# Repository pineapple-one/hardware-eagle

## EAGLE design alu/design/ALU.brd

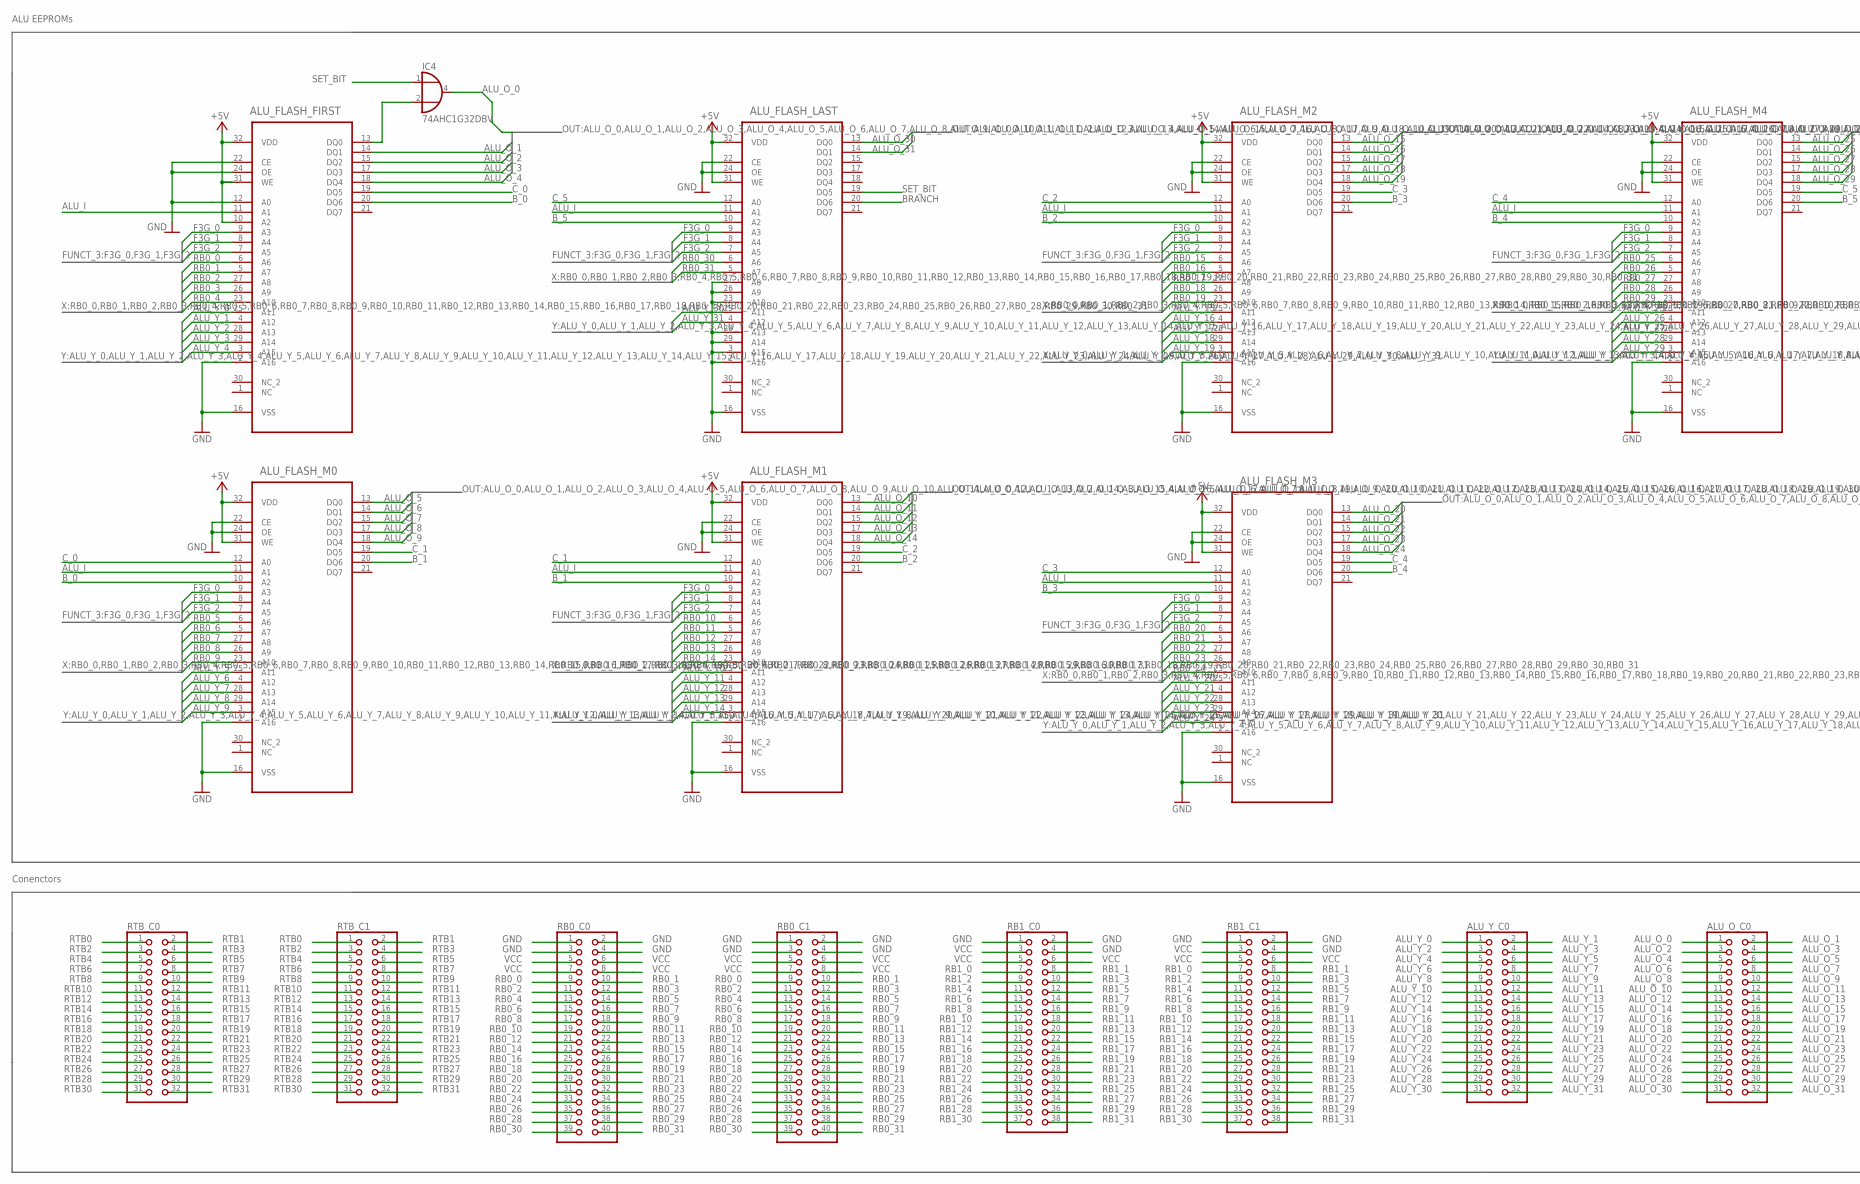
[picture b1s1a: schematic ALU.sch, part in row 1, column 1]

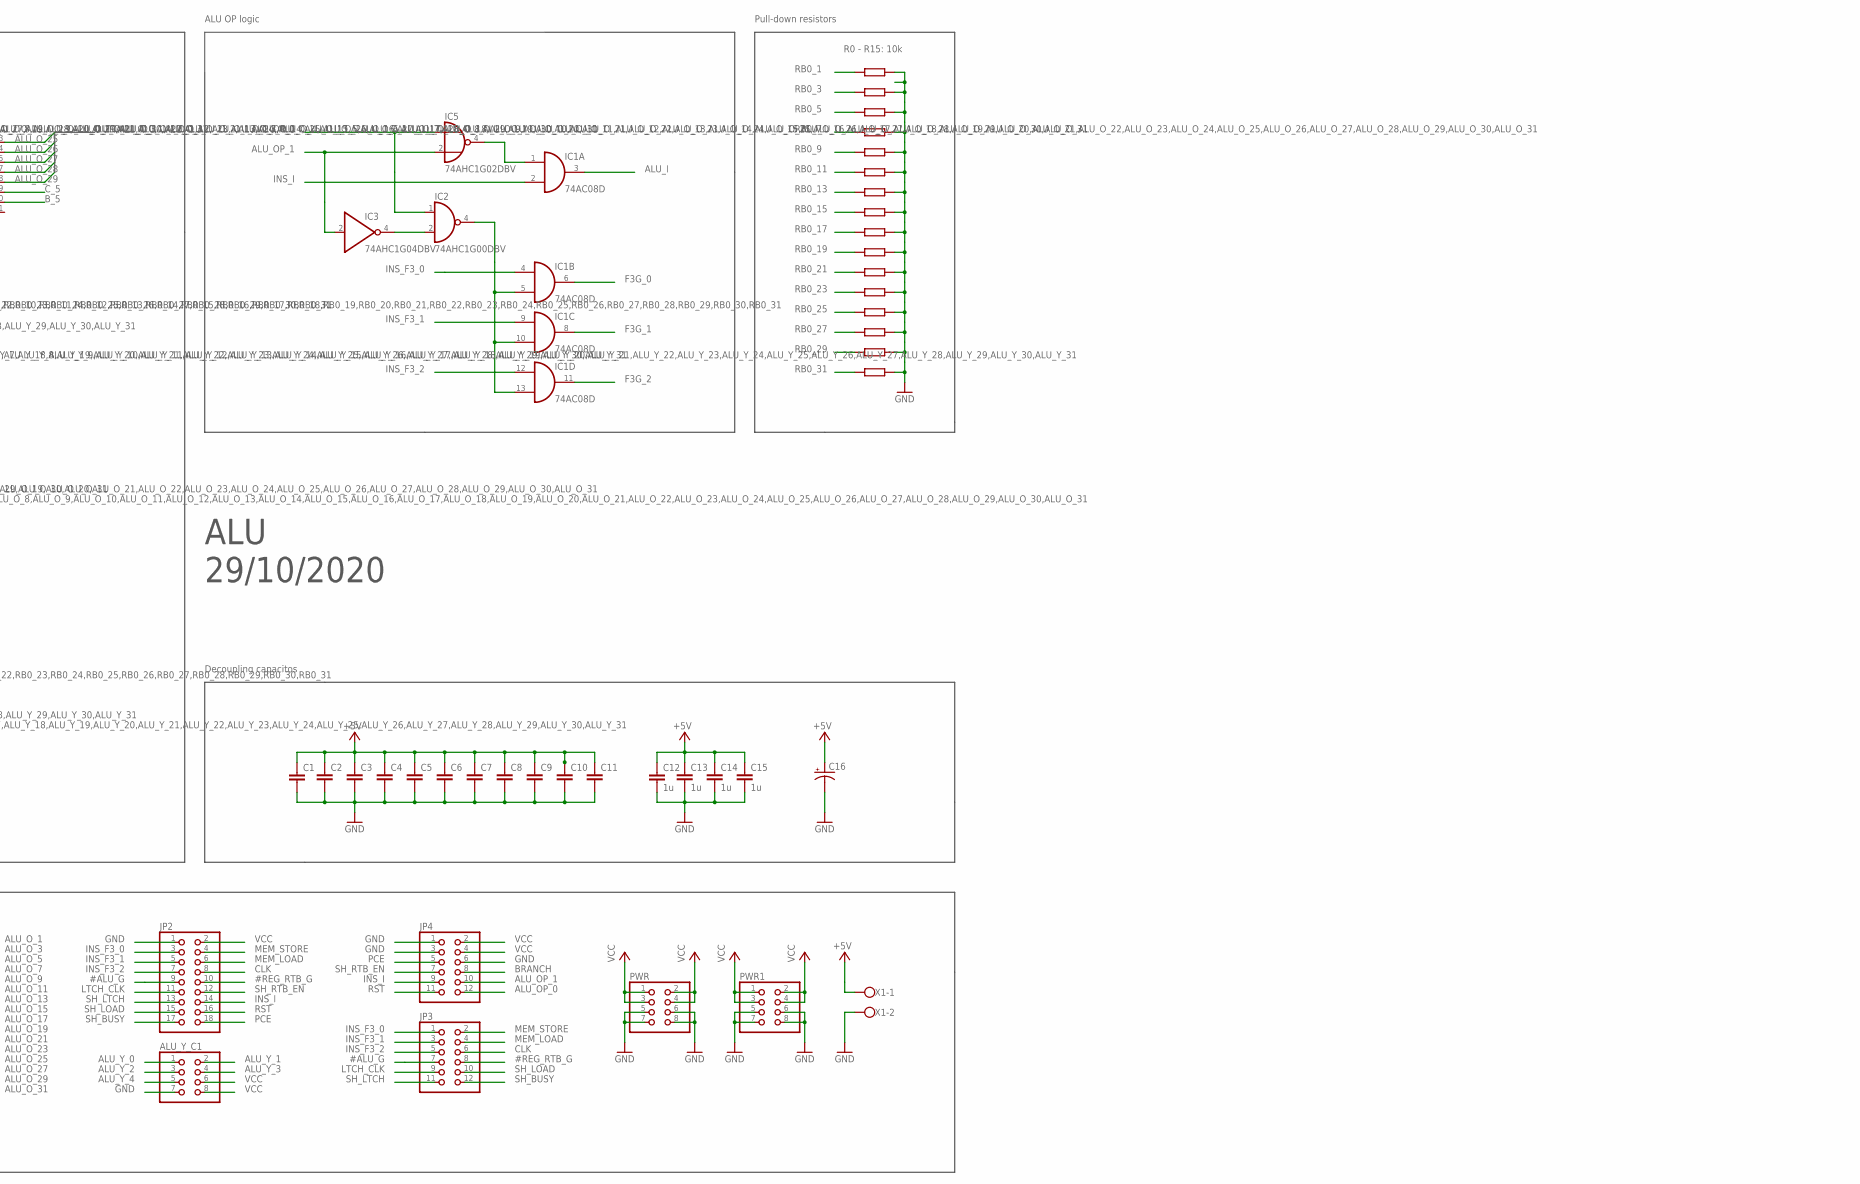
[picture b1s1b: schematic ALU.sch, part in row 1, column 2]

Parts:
ALU_FLASH_FIRST: SST39SF010A-70-4I-NHEPLCC32; S32
ALU_FLASH_LAST: SST39SF010A-70-4I-NHEPLCC32; S32
ALU_FLASH_M0, ALU_FLASH_M1, ALU_FLASH_M2, ALU_FLASH_M3, ALU_FLASH_M4: SST39SF010A-70-4I-NHEPLCC32; S32
ALU_O_C0: PINHD-2X16; 2X16
ALU_Y_C0: PINHD-2X16; 2X16
ALU_Y_C1: PINHD-2X4; 2X04
C1, C2, C3, C4, C5, C6, C7, C8, C9, C10, C11: C-EUC0805; C0805
C12, C13, C14, C15: 1u; C0805
C16: CAPACITOR-P153CLV-1010; 153CLV-1010
IC1: 74AC08D; SO14
IC2: 74AHC1G00DBV; SOT23-5
IC3: 74AHC1G04DBV; SOT23-5
IC4: 74AHC1G32DBV; SOT23-5
IC5: 74AHC1G02DBV; SOT23-5
JP2: PINHD-2X9; 2X09
JP3, JP4: PINHD-2X6; 2X06
PWR, PWR1: PINHD-2X4; 2X04
R0, R1, R2, R3, R4, R5, R6, R7, R8, R9, R10, R11, R12, R13, R14, R15: R-EU_R0805; R0805
RB0_C0, RB0_C1: PINHD-2X20; 2X20
RB1_C0, RB1_C1: PINHD-2X19; 2X19
RTB_C0, RTB_C1: PINHD-2X16; 2X16
X1: W237-102

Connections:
#ALU_G: JP2.9, JP3.7
#REG_RTB_G: JP2.10, JP3.8
ALU_I: ALU_FLASH_FIRST.11 (A1), ALU_FLASH_LAST.11 (A1), ALU_FLASH_M0.11 (A1), ALU_FLASH_M1.11 (A1), ALU_FLASH_M2.11 (A1), ALU_FLASH_M3.11 (A1), ALU_FLASH_M4.11 (A1), IC1.3 (O)
ALU_OP_0: IC2.1 (I0), IC5.1 (I0), JP4.12
ALU_OP_1: IC3.2 (I), IC5.2 (I1), JP4.10
ALU_O_0: ALU_O_C0.1, IC4.4 (O)
ALU_O_1: ALU_FLASH_FIRST.14 (DQ1), ALU_O_C0.2
ALU_O_2: ALU_FLASH_FIRST.15 (DQ2), ALU_O_C0.3
ALU_O_3: ALU_FLASH_FIRST.17 (DQ3), ALU_O_C0.4
ALU_O_4: ALU_FLASH_FIRST.18 (DQ4), ALU_O_C0.5
ALU_O_5: ALU_FLASH_M0.13 (DQ0), ALU_O_C0.6
ALU_O_6: ALU_FLASH_M0.14 (DQ1), ALU_O_C0.7
ALU_O_7: ALU_FLASH_M0.15 (DQ2), ALU_O_C0.8
ALU_O_8: ALU_FLASH_M0.17 (DQ3), ALU_O_C0.9
ALU_O_9: ALU_FLASH_M0.18 (DQ4), ALU_O_C0.10
ALU_O_10: ALU_FLASH_M1.13 (DQ0), ALU_O_C0.11
ALU_O_11: ALU_FLASH_M1.14 (DQ1), ALU_O_C0.12
ALU_O_12: ALU_FLASH_M1.15 (DQ2), ALU_O_C0.13
ALU_O_13: ALU_FLASH_M1.17 (DQ3), ALU_O_C0.14
ALU_O_14: ALU_FLASH_M1.18 (DQ4), ALU_O_C0.15
ALU_O_15: ALU_FLASH_M2.13 (DQ0), ALU_O_C0.16
ALU_O_16: ALU_FLASH_M2.14 (DQ1), ALU_O_C0.17
ALU_O_17: ALU_FLASH_M2.15 (DQ2), ALU_O_C0.18
ALU_O_18: ALU_FLASH_M2.17 (DQ3), ALU_O_C0.19
ALU_O_19: ALU_FLASH_M2.18 (DQ4), ALU_O_C0.20
ALU_O_20: ALU_FLASH_M3.13 (DQ0), ALU_O_C0.21
ALU_O_21: ALU_FLASH_M3.14 (DQ1), ALU_O_C0.22
ALU_O_22: ALU_FLASH_M3.15 (DQ2), ALU_O_C0.23
ALU_O_23: ALU_FLASH_M3.17 (DQ3), ALU_O_C0.24
ALU_O_24: ALU_FLASH_M3.18 (DQ4), ALU_O_C0.25
ALU_O_25: ALU_FLASH_M4.13 (DQ0), ALU_O_C0.26
ALU_O_26: ALU_FLASH_M4.14 (DQ1), ALU_O_C0.27
ALU_O_27: ALU_FLASH_M4.15 (DQ2), ALU_O_C0.28
ALU_O_28: ALU_FLASH_M4.17 (DQ3), ALU_O_C0.29
ALU_O_29: ALU_FLASH_M4.18 (DQ4), ALU_O_C0.30
ALU_O_30: ALU_FLASH_LAST.13 (DQ0), ALU_O_C0.31
ALU_O_31: ALU_FLASH_LAST.14 (DQ1), ALU_O_C0.32
ALU_Y_0: ALU_FLASH_FIRST.25 (A11), ALU_Y_C0.1, ALU_Y_C1.1
ALU_Y_1: ALU_FLASH_FIRST.4 (A12), ALU_Y_C0.2, ALU_Y_C1.2
ALU_Y_2: ALU_FLASH_FIRST.28 (A13), ALU_Y_C0.3, ALU_Y_C1.3
ALU_Y_3: ALU_FLASH_FIRST.29 (A14), ALU_Y_C0.4, ALU_Y_C1.4
ALU_Y_4: ALU_FLASH_FIRST.3 (A15), ALU_Y_C0.5, ALU_Y_C1.5
ALU_Y_5: ALU_FLASH_M0.25 (A11), ALU_Y_C0.6
ALU_Y_6: ALU_FLASH_M0.4 (A12), ALU_Y_C0.7
ALU_Y_7: ALU_FLASH_M0.28 (A13), ALU_Y_C0.8
ALU_Y_8: ALU_FLASH_M0.29 (A14), ALU_Y_C0.9
ALU_Y_9: ALU_FLASH_M0.3 (A15), ALU_Y_C0.10
ALU_Y_10: ALU_FLASH_M1.25 (A11), ALU_Y_C0.11
ALU_Y_11: ALU_FLASH_M1.4 (A12), ALU_Y_C0.12
ALU_Y_12: ALU_FLASH_M1.28 (A13), ALU_Y_C0.13
ALU_Y_13: ALU_FLASH_M1.29 (A14), ALU_Y_C0.14
ALU_Y_14: ALU_FLASH_M1.3 (A15), ALU_Y_C0.15
ALU_Y_15: ALU_FLASH_M2.25 (A11), ALU_Y_C0.16
ALU_Y_16: ALU_FLASH_M2.4 (A12), ALU_Y_C0.17
ALU_Y_17: ALU_FLASH_M2.28 (A13), ALU_Y_C0.18
ALU_Y_18: ALU_FLASH_M2.29 (A14), ALU_Y_C0.19
ALU_Y_19: ALU_FLASH_M2.3 (A15), ALU_Y_C0.20
ALU_Y_20: ALU_FLASH_M3.25 (A11), ALU_Y_C0.21
ALU_Y_21: ALU_FLASH_M3.4 (A12), ALU_Y_C0.22
ALU_Y_22: ALU_FLASH_M3.28 (A13), ALU_Y_C0.23
ALU_Y_23: ALU_FLASH_M3.29 (A14), ALU_Y_C0.24
ALU_Y_24: ALU_FLASH_M3.3 (A15), ALU_Y_C0.25
ALU_Y_25: ALU_FLASH_M4.25 (A11), ALU_Y_C0.26
ALU_Y_26: ALU_FLASH_M4.4 (A12), ALU_Y_C0.27
ALU_Y_27: ALU_FLASH_M4.28 (A13), ALU_Y_C0.28
ALU_Y_28: ALU_FLASH_M4.29 (A14), ALU_Y_C0.29
ALU_Y_29: ALU_FLASH_M4.3 (A15), ALU_Y_C0.30
ALU_Y_30: ALU_FLASH_LAST.25 (A11), ALU_Y_C0.31
ALU_Y_31: ALU_FLASH_LAST.4 (A12), ALU_Y_C0.32
BRANCH: ALU_FLASH_LAST.20 (DQ6), JP4.8
B_0: ALU_FLASH_FIRST.20 (DQ6), ALU_FLASH_M0.10 (A2)
B_1: ALU_FLASH_M0.20 (DQ6), ALU_FLASH_M1.10 (A2)
B_2: ALU_FLASH_M1.20 (DQ6), ALU_FLASH_M2.10 (A2)
B_3: ALU_FLASH_M2.20 (DQ6), ALU_FLASH_M3.10 (A2)
B_4: ALU_FLASH_M3.20 (DQ6), ALU_FLASH_M4.10 (A2)
B_5: ALU_FLASH_LAST.10 (A2), ALU_FLASH_M4.20 (DQ6)
CLK: JP2.8, JP3.6
C_0: ALU_FLASH_FIRST.19 (DQ5), ALU_FLASH_M0.12 (A0)
C_1: ALU_FLASH_M0.19 (DQ5), ALU_FLASH_M1.12 (A0)
C_2: ALU_FLASH_M1.19 (DQ5), ALU_FLASH_M2.12 (A0)
C_3: ALU_FLASH_M2.19 (DQ5), ALU_FLASH_M3.12 (A0)
C_4: ALU_FLASH_M3.19 (DQ5), ALU_FLASH_M4.12 (A0)
C_5: ALU_FLASH_LAST.12 (A0), ALU_FLASH_M4.19 (DQ5)
F3G_0: ALU_FLASH_FIRST.9 (A3), ALU_FLASH_LAST.9 (A3), ALU_FLASH_M0.9 (A3), ALU_FLASH_M1.9 (A3), ALU_FLASH_M2.9 (A3), ALU_FLASH_M3.9 (A3), ALU_FLASH_M4.9 (A3), IC1.6 (O)
F3G_1: ALU_FLASH_FIRST.8 (A4), ALU_FLASH_LAST.8 (A4), ALU_FLASH_M0.8 (A4), ALU_FLASH_M1.8 (A4), ALU_FLASH_M2.8 (A4), ALU_FLASH_M3.8 (A4), ALU_FLASH_M4.8 (A4), IC1.8 (O)
F3G_2: ALU_FLASH_FIRST.7 (A5), ALU_FLASH_LAST.7 (A5), ALU_FLASH_M0.7 (A5), ALU_FLASH_M1.7 (A5), ALU_FLASH_M2.7 (A5), ALU_FLASH_M3.7 (A5), ALU_FLASH_M4.7 (A5), IC1.11 (O)
GND: ALU_FLASH_FIRST.2 (A16), ALU_FLASH_FIRST.12 (A0), ALU_FLASH_FIRST.16 (VSS), ALU_FLASH_FIRST.22 (CE), ALU_FLASH_FIRST.24 (OE), ALU_FLASH_LAST.2 (A16), ALU_FLASH_LAST.3 (A15), ALU_FLASH_LAST.16 (VSS), ALU_FLASH_LAST.22 (CE), ALU_FLASH_LAST.23 (A10), ALU_FLASH_LAST.24 (OE), ALU_FLASH_LAST.26 (A9), ALU_FLASH_LAST.27 (A8), ALU_FLASH_LAST.28 (A13), ALU_FLASH_LAST.29 (A14), ALU_FLASH_M0.2 (A16), ALU_FLASH_M0.16 (VSS), ALU_FLASH_M0.22 (CE), ALU_FLASH_M0.24 (OE), ALU_FLASH_M1.2 (A16), ALU_FLASH_M1.16 (VSS), ALU_FLASH_M1.22 (CE), ALU_FLASH_M1.24 (OE), ALU_FLASH_M2.2 (A16), ALU_FLASH_M2.16 (VSS), ALU_FLASH_M2.22 (CE), ALU_FLASH_M2.24 (OE), ALU_FLASH_M3.2 (A16), ALU_FLASH_M3.16 (VSS), ALU_FLASH_M3.22 (CE), ALU_FLASH_M3.24 (OE), ALU_FLASH_M4.2 (A16), ALU_FLASH_M4.16 (VSS), ALU_FLASH_M4.22 (CE), ALU_FLASH_M4.24 (OE), ALU_Y_C1.7, C1.2, C2.2, C3.2, C4.2, C5.2, C6.2, C7.2, C8.2, C9.2, C10.2, C11.2, C12.2, C13.2, C14.2, C15.2, C16.-, IC1.7 (GND), IC2.3 (GND), IC3.3 (GND), IC4.3 (GND), IC5.3 (GND), JP2.1, JP4.1, JP4.3, JP4.6, PWR.5, PWR.6, PWR.7, PWR.8, PWR1.5, PWR1.6, PWR1.7, PWR1.8, R0.2, R1.2, R2.2, R3.2, R4.2, R5.2, R6.2, R7.2, R8.2, R9.2, R10.2, R11.2, R12.2, R13.2, R14.2, R15.2, RB0_C0.1, RB0_C0.2, RB0_C0.3, RB0_C0.4, RB0_C1.1, RB0_C1.2, RB0_C1.3, RB0_C1.4, RB1_C0.1, RB1_C0.2, RB1_C0.4, RB1_C1.1, RB1_C1.2, RB1_C1.4, X1.2
INS_F3_0: IC1.4 (I0), JP2.3, JP3.1
INS_F3_1: IC1.9 (I0), JP2.5, JP3.3
INS_F3_2: IC1.12 (I0), JP2.7, JP3.5
INS_I: IC1.2 (I1), JP2.14, JP4.9
LTCH_CLK: JP2.11, JP3.9
MEM_LOAD: JP2.6, JP3.4
MEM_STORE: JP2.4, JP3.2
unnamed: ALU_FLASH_FIRST.13 (DQ0), IC4.2 (I1)
unnamed: IC1.5 (I1), IC1.10 (I1), IC1.13 (I1), IC2.4 (O)
unnamed: IC2.2 (I1), IC3.4 (O)
unnamed: IC1.1 (I0), IC5.4 (O)
PCE: JP2.18, JP4.5
RB0_0: ALU_FLASH_FIRST.6 (A6), RB0_C0.9, RB0_C1.9
RB0_1: ALU_FLASH_FIRST.5 (A7), R0.1, RB0_C0.10, RB0_C1.10
RB0_2: ALU_FLASH_FIRST.27 (A8), RB0_C0.11, RB0_C1.11
RB0_3: ALU_FLASH_FIRST.26 (A9), R1.1, RB0_C0.12, RB0_C1.12
RB0_4: ALU_FLASH_FIRST.23 (A10), RB0_C0.13, RB0_C1.13
RB0_5: ALU_FLASH_M0.6 (A6), R2.1, RB0_C0.14, RB0_C1.14
RB0_6: ALU_FLASH_M0.5 (A7), RB0_C0.15, RB0_C1.15
RB0_7: ALU_FLASH_M0.27 (A8), R3.1, RB0_C0.16, RB0_C1.16
RB0_8: ALU_FLASH_M0.26 (A9), RB0_C0.17, RB0_C1.17
RB0_9: ALU_FLASH_M0.23 (A10), R4.1, RB0_C0.18, RB0_C1.18
RB0_10: ALU_FLASH_M1.6 (A6), RB0_C0.19, RB0_C1.19
RB0_11: ALU_FLASH_M1.5 (A7), R5.1, RB0_C0.20, RB0_C1.20
RB0_12: ALU_FLASH_M1.27 (A8), RB0_C0.21, RB0_C1.21
RB0_13: ALU_FLASH_M1.26 (A9), R6.1, RB0_C0.22, RB0_C1.22
RB0_14: ALU_FLASH_M1.23 (A10), RB0_C0.23, RB0_C1.23
RB0_15: ALU_FLASH_M2.6 (A6), R7.1, RB0_C0.24, RB0_C1.24
RB0_16: ALU_FLASH_M2.5 (A7), RB0_C0.25, RB0_C1.25
RB0_17: ALU_FLASH_M2.27 (A8), R8.1, RB0_C0.26, RB0_C1.26
RB0_18: ALU_FLASH_M2.26 (A9), RB0_C0.27, RB0_C1.27
RB0_19: ALU_FLASH_M2.23 (A10), R9.1, RB0_C0.28, RB0_C1.28
RB0_20: ALU_FLASH_M3.6 (A6), RB0_C0.29, RB0_C1.29
RB0_21: ALU_FLASH_M3.5 (A7), R10.1, RB0_C0.30, RB0_C1.30
RB0_22: ALU_FLASH_M3.27 (A8), RB0_C0.31, RB0_C1.31
RB0_23: ALU_FLASH_M3.26 (A9), R11.1, RB0_C0.32, RB0_C1.32
RB0_24: ALU_FLASH_M3.23 (A10), RB0_C0.33, RB0_C1.33
RB0_25: ALU_FLASH_M4.6 (A6), R12.1, RB0_C0.34, RB0_C1.34
RB0_26: ALU_FLASH_M4.5 (A7), RB0_C0.35, RB0_C1.35
RB0_27: ALU_FLASH_M4.27 (A8), R13.1, RB0_C0.36, RB0_C1.36
RB0_28: ALU_FLASH_M4.26 (A9), RB0_C0.37, RB0_C1.37
RB0_29: ALU_FLASH_M4.23 (A10), R14.1, RB0_C0.38, RB0_C1.38
RB0_30: ALU_FLASH_LAST.6 (A6), RB0_C0.39, RB0_C1.39
RB0_31: ALU_FLASH_LAST.5 (A7), R15.1, RB0_C0.40, RB0_C1.40
RB1_0: RB1_C0.7, RB1_C1.7
RB1_1: RB1_C0.8, RB1_C1.8
RB1_2: RB1_C0.9, RB1_C1.9
RB1_3: RB1_C0.10, RB1_C1.10
RB1_4: RB1_C0.11, RB1_C1.11
RB1_5: RB1_C0.12, RB1_C1.12
RB1_6: RB1_C0.13, RB1_C1.13
RB1_7: RB1_C0.14, RB1_C1.14
RB1_8: RB1_C0.15, RB1_C1.15
RB1_9: RB1_C0.16, RB1_C1.16
RB1_10: RB1_C0.17, RB1_C1.17
RB1_11: RB1_C0.18, RB1_C1.18
RB1_12: RB1_C0.19, RB1_C1.19
RB1_13: RB1_C0.20, RB1_C1.20
RB1_14: RB1_C0.21, RB1_C1.21
RB1_15: RB1_C0.22, RB1_C1.22
RB1_16: RB1_C0.23, RB1_C1.23
RB1_17: RB1_C0.24, RB1_C1.24
RB1_18: RB1_C0.25, RB1_C1.25
RB1_19: RB1_C0.26, RB1_C1.26
RB1_20: RB1_C0.27, RB1_C1.27
RB1_21: RB1_C0.28, RB1_C1.28
RB1_22: RB1_C0.29, RB1_C1.29
RB1_23: RB1_C0.30, RB1_C1.30
RB1_24: RB1_C0.31, RB1_C1.31
RB1_25: RB1_C0.32, RB1_C1.32
RB1_26: RB1_C0.33, RB1_C1.33
RB1_27: RB1_C0.34, RB1_C1.34
RB1_28: RB1_C0.35, RB1_C1.35
RB1_29: RB1_C0.36, RB1_C1.36
RB1_30: RB1_C0.37, RB1_C1.37
RB1_31: RB1_C0.38, RB1_C1.38
RST: JP2.16, JP4.11
RTB0: RTB_C0.1, RTB_C1.1
RTB1: RTB_C0.2, RTB_C1.2
RTB2: RTB_C0.3, RTB_C1.3
RTB3: RTB_C0.4, RTB_C1.4
RTB4: RTB_C0.5, RTB_C1.5
RTB5: RTB_C0.6, RTB_C1.6
RTB6: RTB_C0.7, RTB_C1.7
RTB7: RTB_C0.8, RTB_C1.8
RTB8: RTB_C0.9, RTB_C1.9
RTB9: RTB_C0.10, RTB_C1.10
RTB10: RTB_C0.11, RTB_C1.11
RTB11: RTB_C0.12, RTB_C1.12
RTB12: RTB_C0.13, RTB_C1.13
RTB13: RTB_C0.14, RTB_C1.14
RTB14: RTB_C0.15, RTB_C1.15
RTB15: RTB_C0.16, RTB_C1.16
RTB16: RTB_C0.17, RTB_C1.17
RTB17: RTB_C0.18, RTB_C1.18
RTB18: RTB_C0.19, RTB_C1.19
RTB19: RTB_C0.20, RTB_C1.20
RTB20: RTB_C0.21, RTB_C1.21
RTB21: RTB_C0.22, RTB_C1.22
RTB22: RTB_C0.23, RTB_C1.23
RTB23: RTB_C0.24, RTB_C1.24
RTB24: RTB_C0.25, RTB_C1.25
RTB25: RTB_C0.26, RTB_C1.26
RTB26: RTB_C0.27, RTB_C1.27
RTB27: RTB_C0.28, RTB_C1.28
RTB28: RTB_C0.29, RTB_C1.29
RTB29: RTB_C0.30, RTB_C1.30
RTB30: RTB_C0.31, RTB_C1.31
RTB31: RTB_C0.32, RTB_C1.32
SET_BIT: ALU_FLASH_LAST.19 (DQ5), IC4.1 (I0)
SH_BUSY: JP2.17, JP3.12
SH_LOAD: JP2.15, JP3.10
SH_LTCH: JP2.13, JP3.11
SH_RTB_EN: JP2.12, JP4.7
VCC: ALU_FLASH_FIRST.10 (A2), ALU_FLASH_FIRST.31 (WE), ALU_FLASH_FIRST.32 (VDD), ALU_FLASH_LAST.31 (WE), ALU_FLASH_LAST.32 (VDD), ALU_FLASH_M0.31 (WE), ALU_FLASH_M0.32 (VDD), ALU_FLASH_M1.31 (WE), ALU_FLASH_M1.32 (VDD), ALU_FLASH_M2.31 (WE), ALU_FLASH_M2.32 (VDD), ALU_FLASH_M3.31 (WE), ALU_FLASH_M3.32 (VDD), ALU_FLASH_M4.31 (WE), ALU_FLASH_M4.32 (VDD), ALU_Y_C1.6, ALU_Y_C1.8, C1.1, C2.1, C3.1, C4.1, C5.1, C6.1, C7.1, C8.1, C9.1, C10.1, C11.1, C12.1, C13.1, C14.1, C15.1, C16.+, IC1.14 (VCC), IC2.5 (VCC), IC3.5 (VCC), IC4.5 (VCC), IC5.5 (VCC), JP2.2, JP4.2, JP4.4, PWR.1, PWR.2, PWR.3, PWR.4, PWR1.1, PWR1.2, PWR1.3, PWR1.4, RB0_C0.5, RB0_C0.6, RB0_C0.7, RB0_C0.8, RB0_C1.5, RB0_C1.6, RB0_C1.7, RB0_C1.8, RB1_C0.3, RB1_C0.5, RB1_C0.6, RB1_C1.3, RB1_C1.5, RB1_C1.6, X1.1

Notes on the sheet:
R0 - R15: 10k
ALU EEPROMs
Conenctors
ALU OP logic
Decoupling capacitos
Pull-down resistors
ALU 29/10/2020

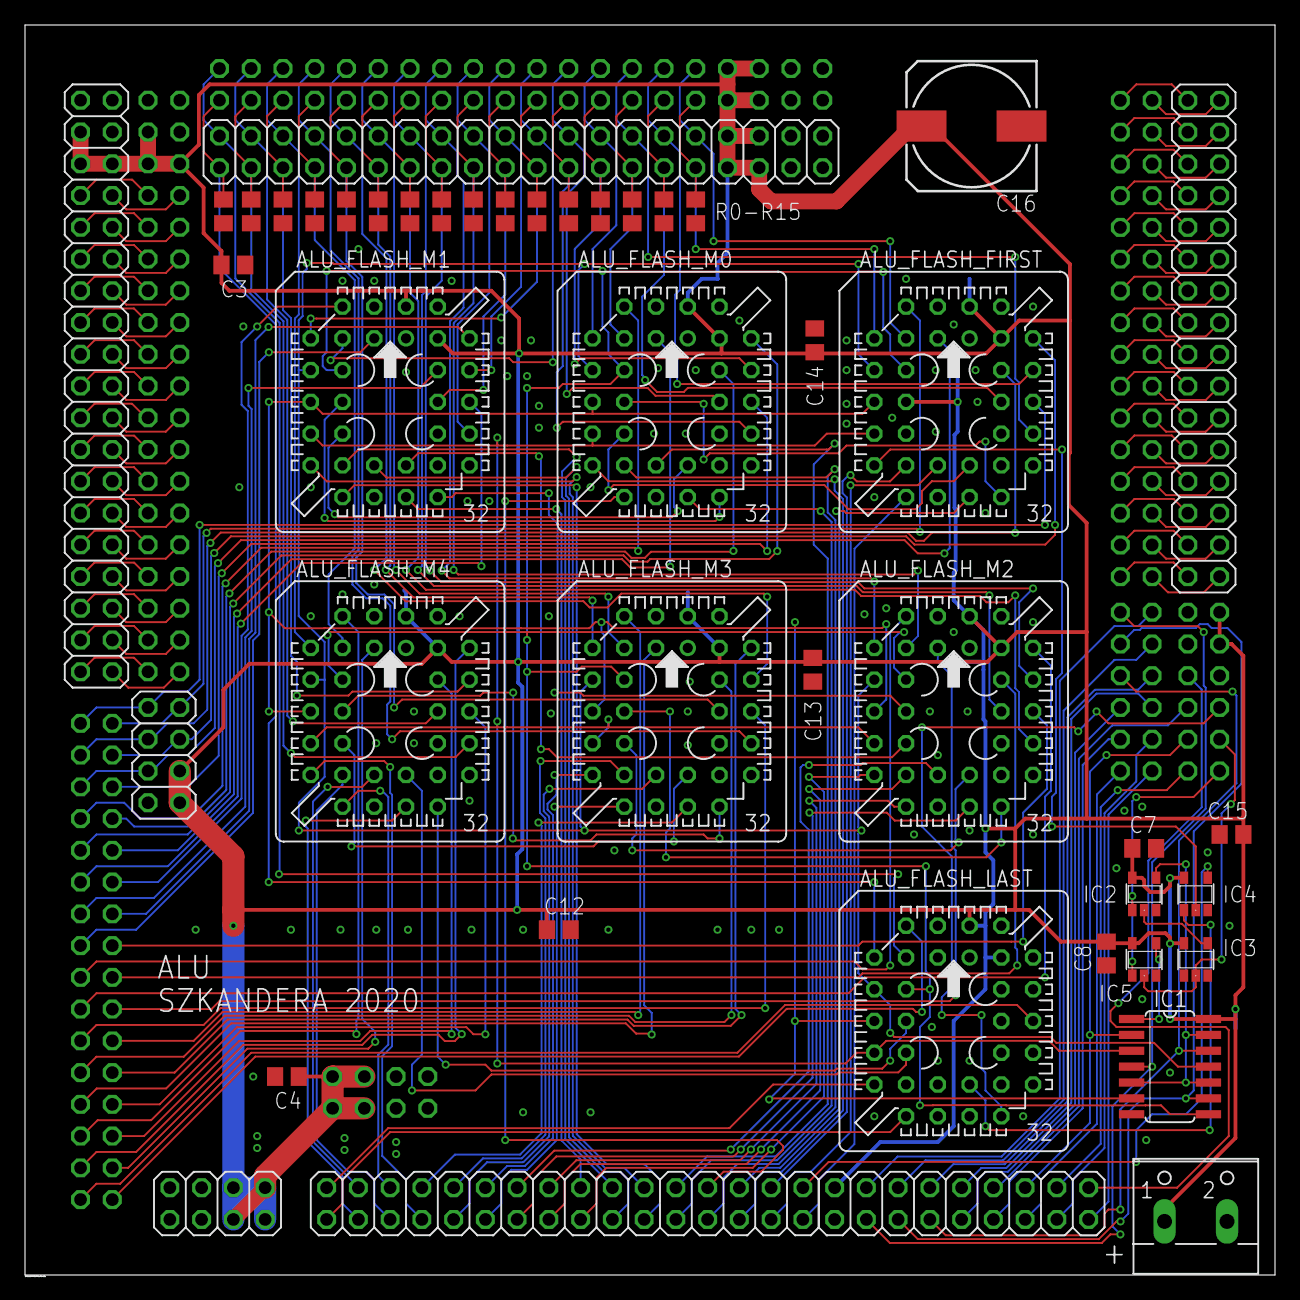
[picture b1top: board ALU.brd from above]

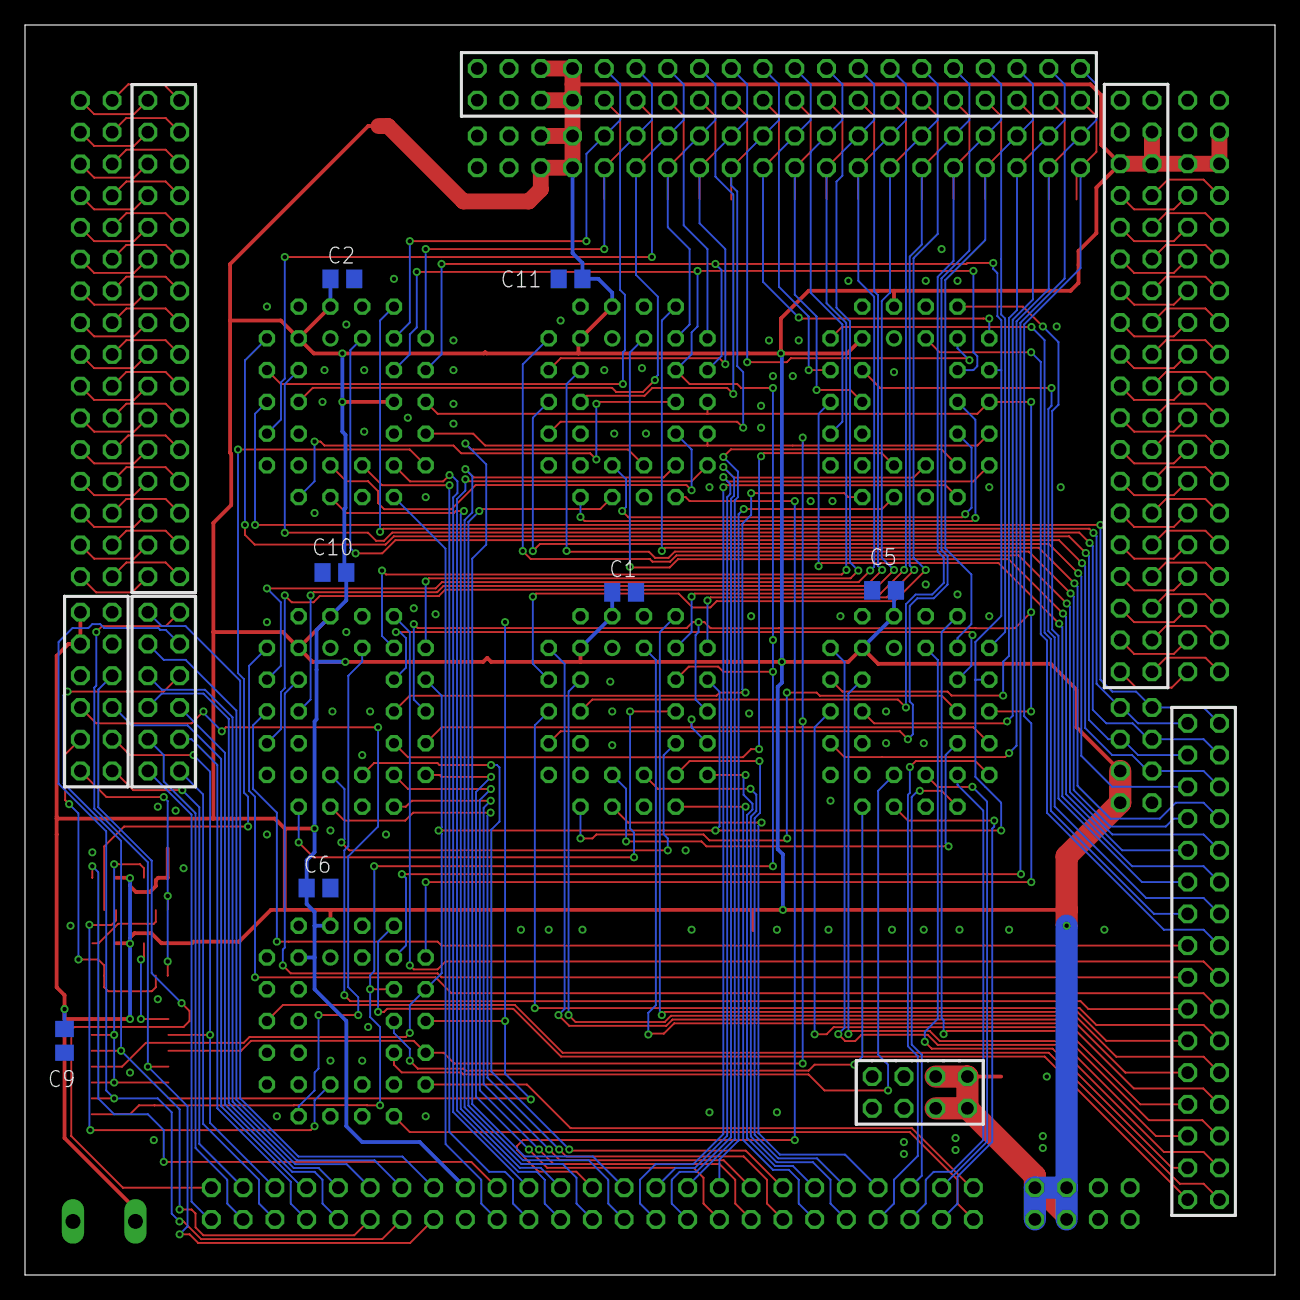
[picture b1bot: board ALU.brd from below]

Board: 2 copper layers, 100.0 x 100.0 mm, 59 parts (7 on the bottom side), 202 nets.
